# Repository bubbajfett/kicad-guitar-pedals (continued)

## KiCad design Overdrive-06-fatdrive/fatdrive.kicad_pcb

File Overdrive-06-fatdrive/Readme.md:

# Fat Drive

This is a clone of the Pigtronice Fad Drive overdrive.  

This also has a very nice crunchy sound.

Changed the board size to 3mm narrower, and that caused the board
to get a new layout that is slightly changed.   Used freerouter with
some manual cleanup.

So this pedal is verified. I have not boxed this one yet, either.

All trademarks belong to their respective owners.

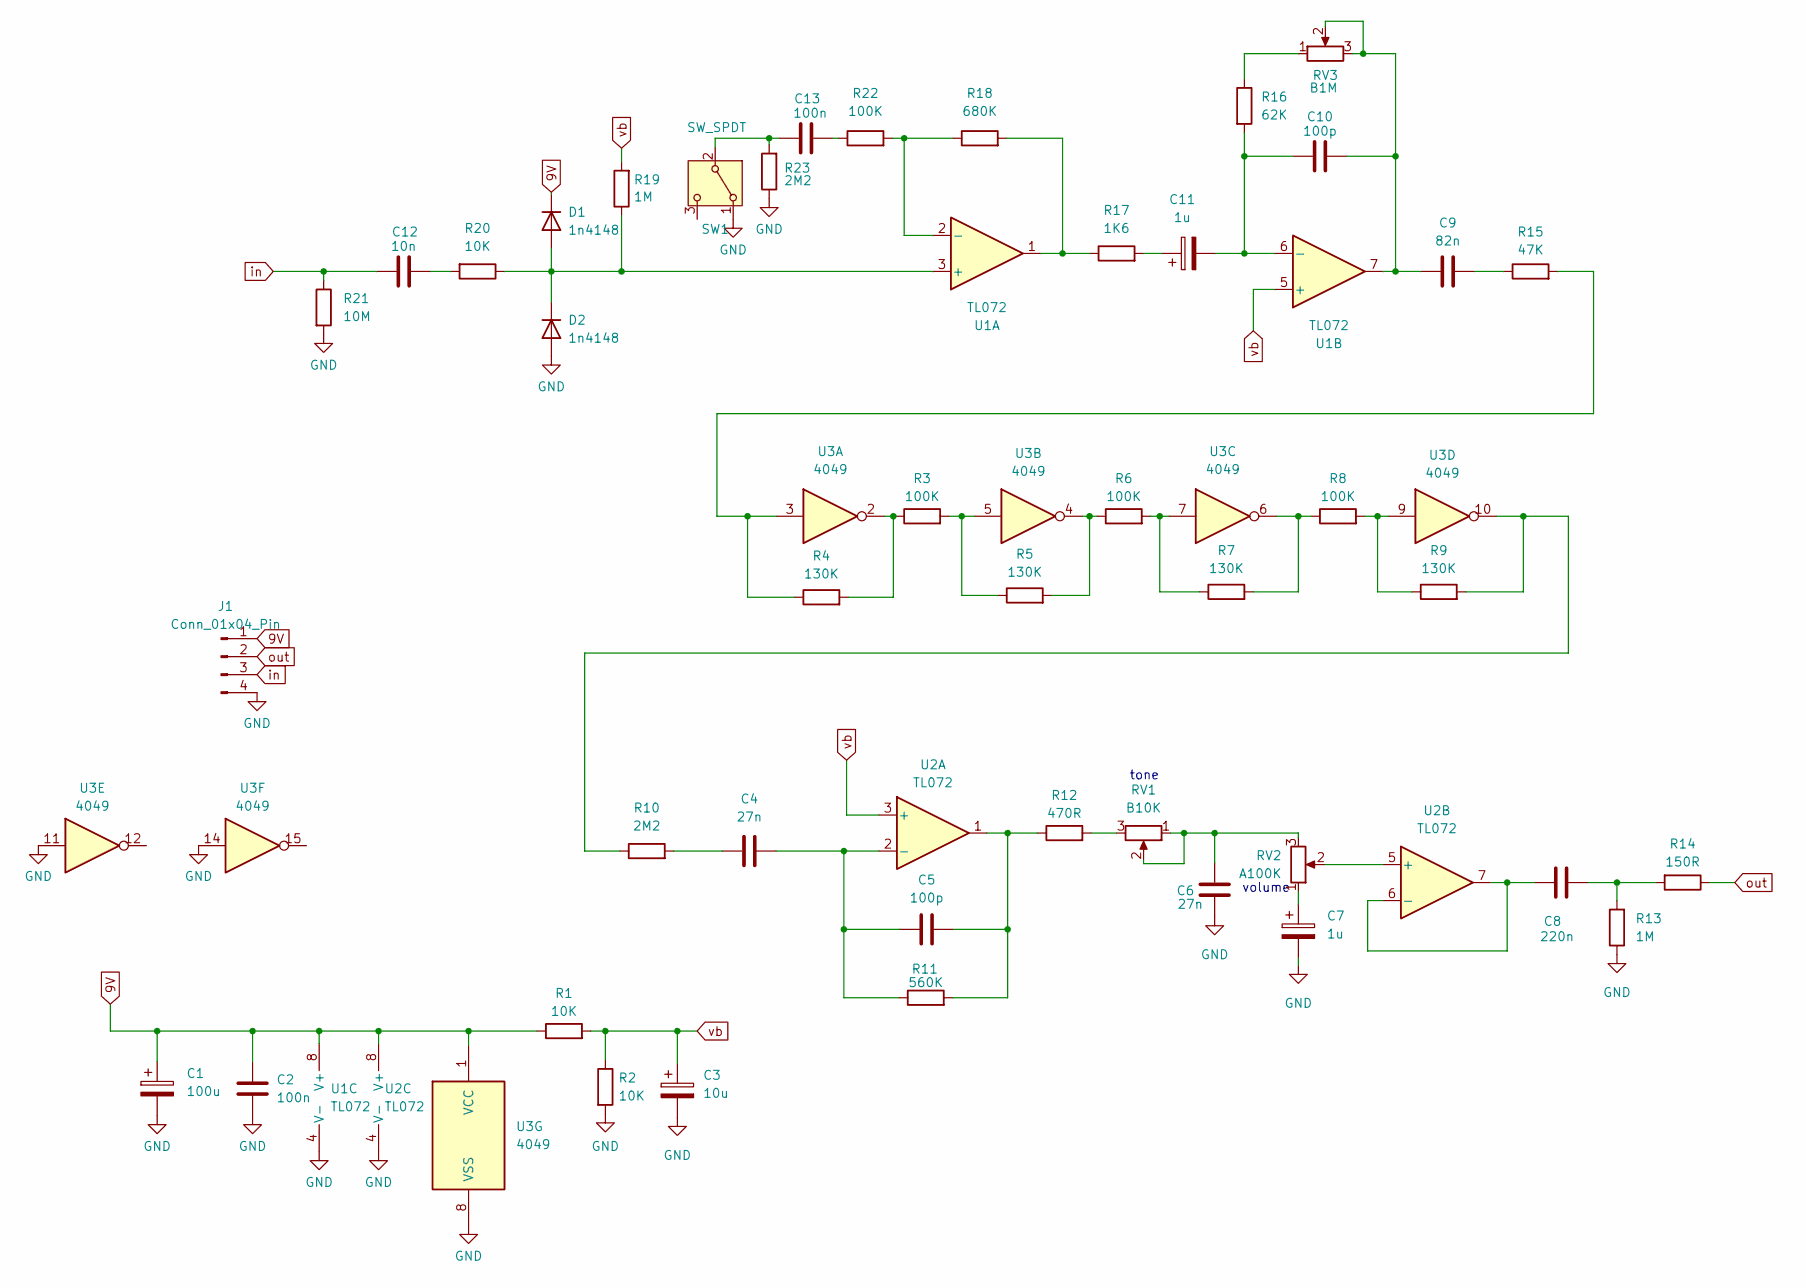
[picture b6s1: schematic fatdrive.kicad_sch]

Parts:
C1: 100u; CP_Radial_D6.3mm_P2.50mm
C2, C13: 100n; C_Disc_D5.0mm_W2.5mm_P5.00mm
C3: 10u; CP_Radial_D5.0mm_P2.00mm
C4, C6: 27n; C_Disc_D5.0mm_W2.5mm_P5.00mm
C5, C10: 100p; C_Disc_D3.0mm_W2.0mm_P2.50mm
C7, C11: 1u; CP_Radial_D5.0mm_P2.00mm
C8: 220n; C_Disc_D5.0mm_W2.5mm_P5.00mm
C9: 82n; C_Disc_D5.0mm_W2.5mm_P5.00mm
C12: 10n; C_Disc_D5.0mm_W2.5mm_P5.00mm
D1, D2: 1n4148; D_A-405_P7.62mm_Horizontal
J1: Conn_01x04_Pin; PinHeader_1x04_P2.54mm_Vertical
R1, R2, R20: 10K; R_Axial_DIN0207_L6.3mm_D2.5mm_P7.62mm_Horizontal
R3, R6, R8, R22: 100K; R_Axial_DIN0207_L6.3mm_D2.5mm_P7.62mm_Horizontal
R4, R5, R7, R9: 130K; R_Axial_DIN0207_L6.3mm_D2.5mm_P7.62mm_Horizontal
R10, R23: 2M2; R_Axial_DIN0207_L6.3mm_D2.5mm_P7.62mm_Horizontal
R11: 560K; R_Axial_DIN0207_L6.3mm_D2.5mm_P7.62mm_Horizontal
R12: 470R; R_Axial_DIN0207_L6.3mm_D2.5mm_P7.62mm_Horizontal
R13, R19: 1M; R_Axial_DIN0207_L6.3mm_D2.5mm_P7.62mm_Horizontal
R14: 150R; R_Axial_DIN0207_L6.3mm_D2.5mm_P7.62mm_Horizontal
R15: 47K; R_Axial_DIN0207_L6.3mm_D2.5mm_P7.62mm_Horizontal
R16: 62K; R_Axial_DIN0207_L6.3mm_D2.5mm_P7.62mm_Horizontal
R17: 1K6; R_Axial_DIN0207_L6.3mm_D2.5mm_P7.62mm_Horizontal
R18: 680K; R_Axial_DIN0207_L6.3mm_D2.5mm_P7.62mm_Horizontal
R21: 10M; R_Axial_DIN0207_L6.3mm_D2.5mm_P7.62mm_Horizontal
RV1: B10K; Pot_Underside
RV2: A100K; Pot_Underside
RV3: B1M; Pot_Underside
SW1: SW_SPDT; SWITCH-M1-SPDT
U1, U2: TL072; DIP-8_W7.62mm
U3: 4049; DIP-16_W7.62mm

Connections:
9V: C1.1, C2.1, D1.1 (K), J1.1, R1.1, U1.8 (V+), U2.8 (V+), U3.1 (VCC)
GND: C1.2, C2.2, C3.2, C6.1, C7.2, D2.2 (A), J1.4, R2.2, R13.1, R21.2, R23.1, SW1.1 (A), U1.4 (V-), U2.4 (V-), U3.8 (VSS), U3.11, U3.14
unnamed: C4.1, R10.2
unnamed: C5.2, R11.2, R12.1, U2.1
unnamed: C6.2, RV1.1, RV1.2, RV2.3
unnamed: C7.1, RV2.1
unnamed: C8.1, R13.2, R14.2
unnamed: C9.2, R15.1
unnamed: C9.1, C10.2, RV3.2, RV3.3, U1.7
unnamed: C11.1, R17.2
unnamed: C12.2, R20.2
unnamed: C13.2, R22.1
unnamed: D1.2 (A), D2.1 (K), R19.1, R20.1, U1.3 (+)
unnamed: R3.1, R4.2, U3.2
unnamed: R3.2, R5.1, U3.5
unnamed: R5.2, R6.1, U3.4
unnamed: R6.2, R7.1, U3.7
unnamed: R7.2, R8.1, U3.6
unnamed: R8.2, R9.1, U3.9
unnamed: R9.2, R10.1, U3.10
unnamed: R12.2, RV1.3
unnamed: R4.1, R15.2, U3.3
unnamed: R16.1, RV3.1
unnamed: R17.1, R18.2, U1.1
unnamed: C13.1, R23.2, SW1.2 (B)
unnamed: R18.1, R22.2, U1.2 (-)
unnamed: C10.1, C11.2, R16.2, U1.6 (-)
unnamed: C4.2, C5.1, R11.1, U2.2 (-)
unnamed: RV2.2, U2.5 (+)
unnamed: C8.2, U2.6 (-), U2.7
in: C12.1, J1.3, R21.1
out: J1.2, R14.1
vb: C3.1, R1.2, R2.1, R19.2, U1.5 (+), U2.3 (+)

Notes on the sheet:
tone
volume

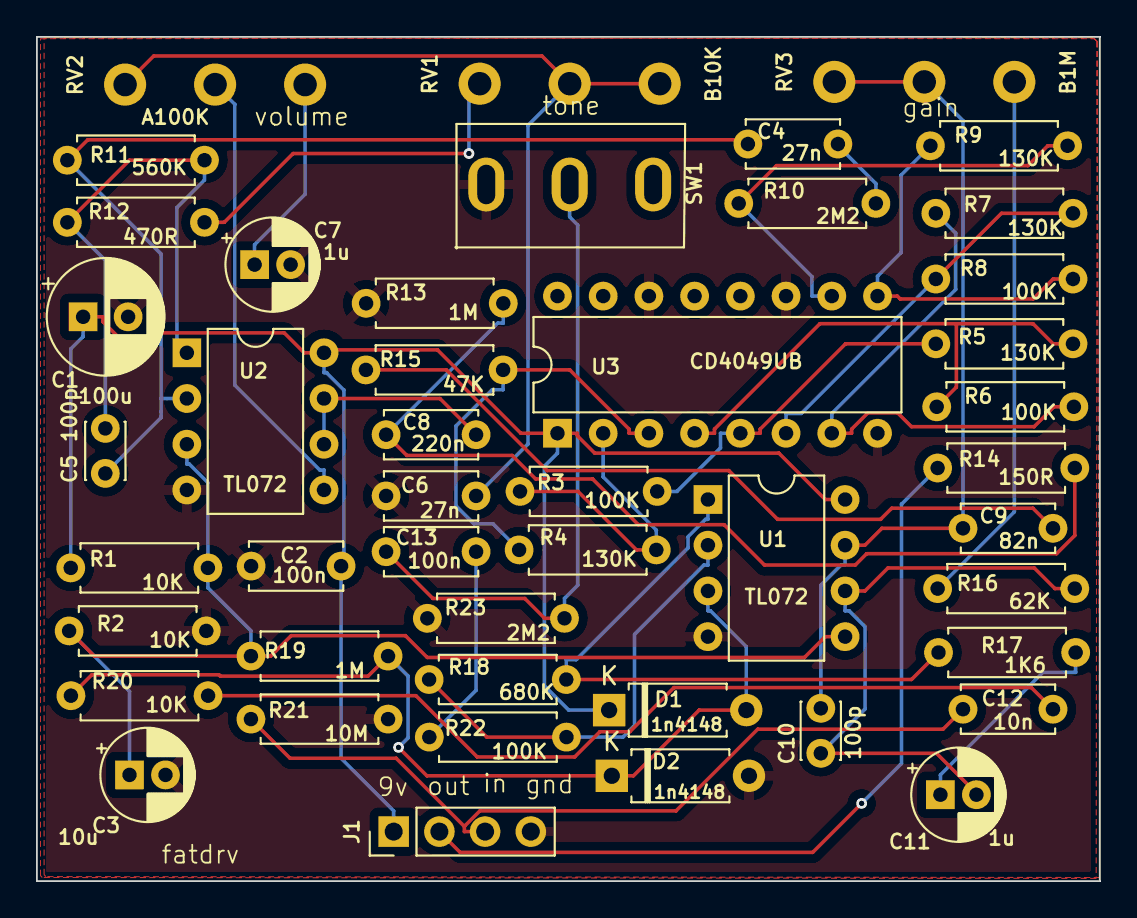
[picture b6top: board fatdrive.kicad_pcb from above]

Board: 2 copper layers, 59.1 x 46.9 mm, 46 parts (0 on the bottom side), 33 nets.

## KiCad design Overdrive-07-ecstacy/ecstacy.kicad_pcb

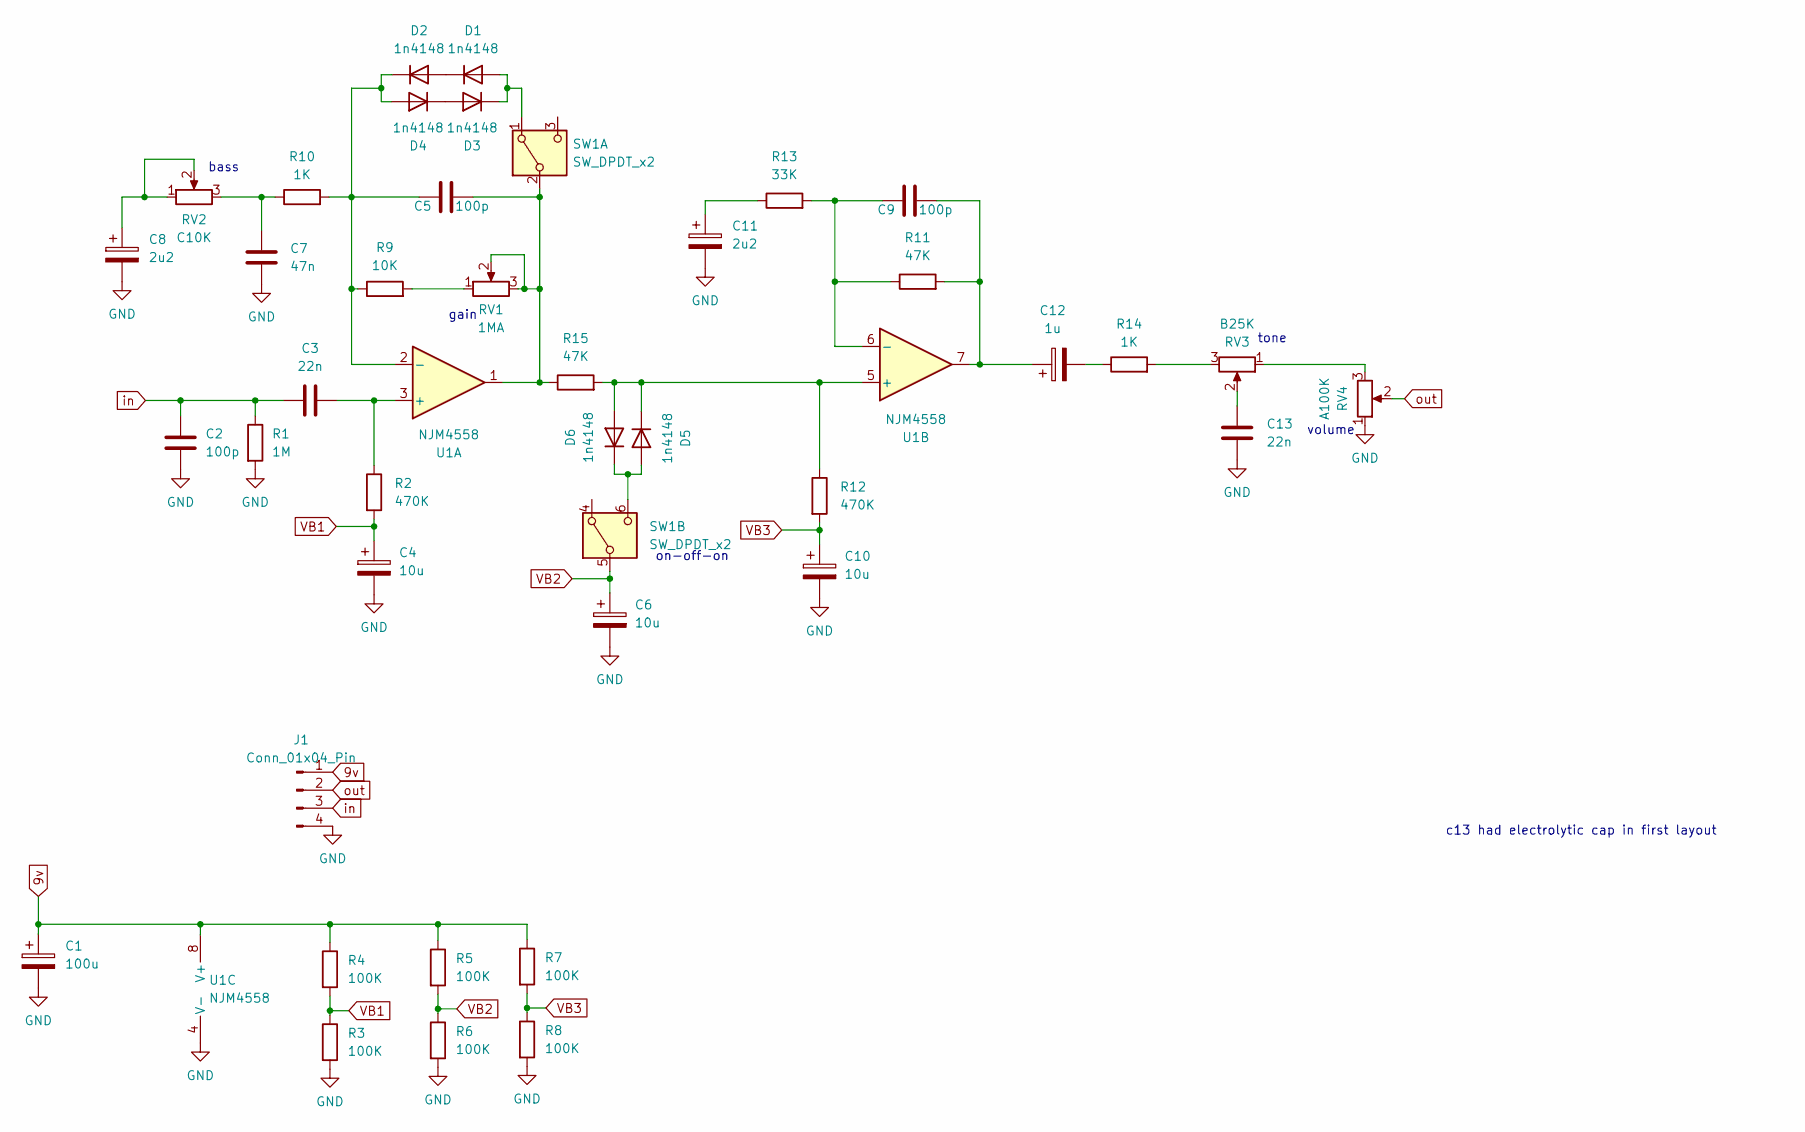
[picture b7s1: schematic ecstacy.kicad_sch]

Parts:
C1: 100u; CP_Radial_D6.3mm_P2.50mm
C2, C5, C9: 100p; C_Disc_D5.0mm_W2.5mm_P5.00mm
C3, C13: 22n; C_Disc_D5.0mm_W2.5mm_P5.00mm
C4, C6, C10: 10u; CP_Radial_D5.0mm_P2.00mm
C7: 47n; C_Disc_D5.0mm_W2.5mm_P5.00mm
C8, C11: 2u2; CP_Radial_D5.0mm_P2.00mm
C12: 1u; CP_Radial_D5.0mm_P2.00mm
D1, D2, D3, D4, D5, D6: 1n4148; D_DO-35_SOD27_P7.62mm_Horizontal
J1: Conn_01x04_Pin; PinHeader_1x04_P2.54mm_Vertical
R1: 1M; R_Axial_DIN0207_L6.3mm_D2.5mm_P7.62mm_Horizontal
R2, R12: 470K; R_Axial_DIN0207_L6.3mm_D2.5mm_P7.62mm_Horizontal
R3, R4, R5, R6, R7, R8: 100K; R_Axial_DIN0207_L6.3mm_D2.5mm_P7.62mm_Horizontal
R9: 10K; R_Axial_DIN0207_L6.3mm_D2.5mm_P7.62mm_Horizontal
R10, R14: 1K; R_Axial_DIN0207_L6.3mm_D2.5mm_P7.62mm_Horizontal
R11, R15: 47K; R_Axial_DIN0207_L6.3mm_D2.5mm_P7.62mm_Horizontal
R13: 33K; R_Axial_DIN0207_L6.3mm_D2.5mm_P7.62mm_Horizontal
RV1: 1MA; Pot_Underside
RV2: C10K; Pot_Underside
RV3: B25K; Pot_Underside
RV4: A100K; Pot_Underside
SW1: SW_DPDT_x2; SWITCH-M1-DPDT
U1: NJM4558; DIP-8_W7.62mm

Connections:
9v: C1.1, J1.1, R4.1, R5.1, R7.1, U1.8 (V+)
GND: C1.2, C2.2, C4.2, C6.2, C7.1, C8.2, C10.2, C11.2, C13.1, J1.4, R1.2, R3.2, R6.2, R8.2, RV4.1, U1.4 (V-)
unnamed: C7.2, R10.1, RV2.3
unnamed: C8.1, RV2.1, RV2.2
unnamed: C11.1, R13.1
unnamed: C9.1, C12.1, R11.2, U1.7
unnamed: C12.2, R14.1
unnamed: C13.2, RV3.2
unnamed: D1.2 (A), D3.1 (K), SW1.1 (A)
unnamed: D1.1 (K), D2.2 (A)
unnamed: C5.2, D2.1 (K), D4.2 (A), R9.1, R10.2, U1.2 (-)
unnamed: D3.2 (A), D4.1 (K)
unnamed: D5.2 (A), D6.1 (K), SW1.6 (C)
unnamed: D5.1 (K), D6.2 (A), R12.1, R15.2, U1.5 (+)
unnamed: R9.2, RV1.1
unnamed: R14.2, RV3.3
unnamed: RV3.1, RV4.3
unnamed: C5.1, R15.1, RV1.2, RV1.3, SW1.2 (B), U1.1
unnamed: C3.2, R2.1, U1.3 (+)
unnamed: C9.2, R11.1, R13.2, U1.6 (-)
VB1: C4.1, R2.2, R3.1, R4.2
VB2: C6.1, R5.2, R6.1, SW1.5 (B)
VB3: C10.1, R7.2, R8.1, R12.2
in: C2.1, C3.1, J1.3, R1.1
out: J1.2, RV4.2

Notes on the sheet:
volume
c13 had electrolytic cap in first layout
bass
on-off-on
tone
gain

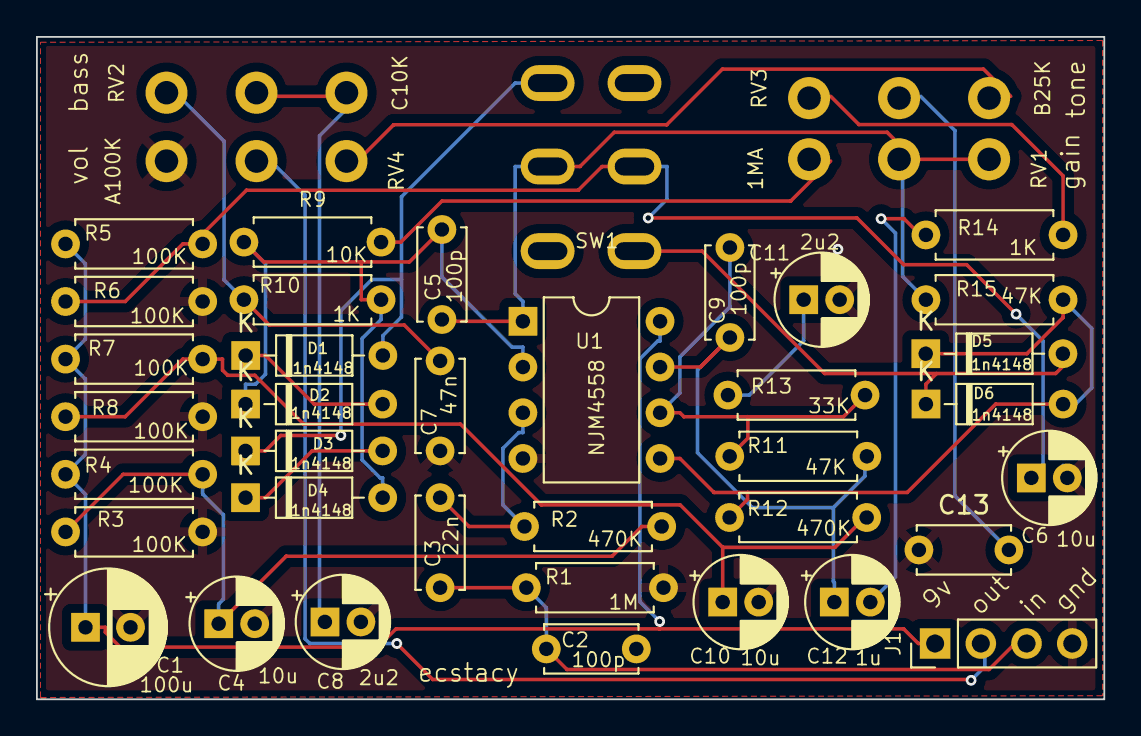
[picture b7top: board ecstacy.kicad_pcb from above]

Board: 2 copper layers, 59.3 x 36.8 mm, 41 parts (0 on the bottom side), 25 nets.
